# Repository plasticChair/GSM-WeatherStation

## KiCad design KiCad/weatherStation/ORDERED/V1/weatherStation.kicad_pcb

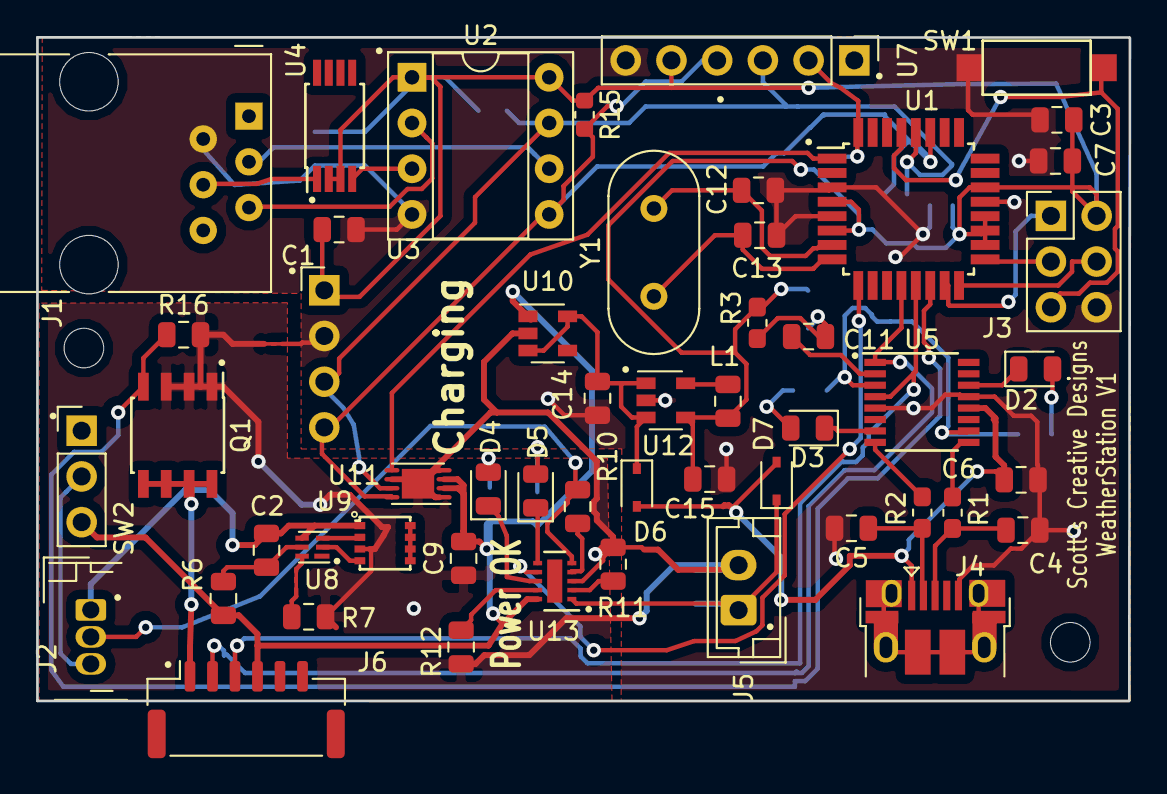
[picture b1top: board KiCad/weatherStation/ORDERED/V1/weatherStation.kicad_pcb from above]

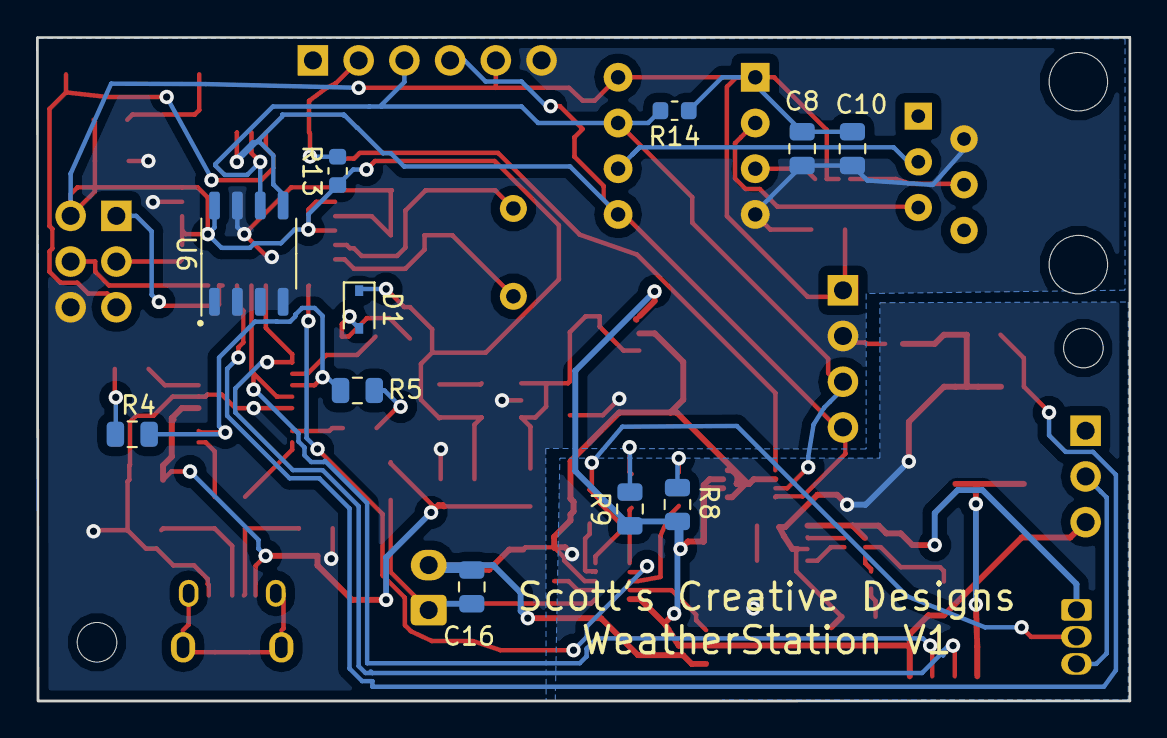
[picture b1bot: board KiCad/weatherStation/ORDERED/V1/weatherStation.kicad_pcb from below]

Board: 2 copper layers, 60.7 x 36.9 mm, 65 parts (11 on the bottom side), 54 nets.

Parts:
C1, C3, C6, C7, C8, C10, C11: 100nF; C_0805_2012Metric
C2, C9, C16: 0.1uF; C_0805_2012Metric
C4, C5: 47pF; C_0805_2012Metric
C12, C13: 22nF; C_0805_2012Metric
C14: 4.7uF; C_0805_2012Metric
C15: 10uF; C_0805_2012Metric
D1: D; D_SOD-323
D2: TXLED; LED_0805_2012Metric
D3: RXLED; LED_0805_2012Metric
D4, D5: LED; LED_0805_2012Metric
D6, D7: D_Schottky; D_SOD-323
J1: RJ12; RJ12_Amphenol_54601
J2: Conn_01x03; JST_EH_B03B-EH-A_1x03_P1.50mm_Vertical
J3: AVR-ISP-6; PinHeader_2x03_P2.54mm_Vertical
J4: USB_B_Micro; USB_Micro-B_Amphenol_10103594-0001LF_Horizontal
J5: Conn_01x02; JST_EH_B02B-EH-A_1x02_P2.50mm_Vertical
J6: Conn_01x04; JST_GH_SM06B-GHS-TB_1x06-1MP_P1.25mm_Horizontal
L1: 2.2uH; L_0805_2012Metric
Q1: AO4430; SOIC-8_3.9x4.9mm_P1.27mm
R1, R2: 27R; R_0603_1608Metric_Pad1.05x0.95mm_HandSolder
R3: 100k; R_0603_1608Metric_Pad1.05x0.95mm_HandSolder
R4, R5: 270R; R_0805_2012Metric
R6, R8, R9, R11, R12, R16: 330; R_0805_2012Metric
R7: 2.2k; R_0805_2012Metric
R10: RT; R_0805_2012Metric
R13: 50k; R_0603_1608Metric
R14, R15: 5k; R_0603_1608Metric
SW1: SW_Push; Tact_SMD_Switch
SW2: SW_SPDT; PinHeader_1x03_P2.54mm_Vertical
U1: ATmega328P-AU; TQFP-32_7x7mm_P0.8mm
U2: ATtiny45V-10PU; DIP-8_W7.62mm_Socket
U3: BME280; PinHeader_1x04_P2.54mm_Horizontal
U4: FDW254p; TSSOP-8_4.4x3mm_P0.65mm
U5: FT230XS; SSOP-16_3.9x4.9mm_P0.635mm
U6: MB85RC64; SSOP-8_3.9x5.05mm_P1.27mm
U7: DS3231_Breakout; PinHeader_1x06_P2.54mm_Vertical
U8: BQ297xy; WSON-6_1.5x1.5mm_P0.5mm
U9: ECH8693R; sot-28
U10: MAX40200; SOT-23-5
U11: MAX17048; TDFN-8-1EP_3x2mm_P0.5mm_EP1.80x1.65mm
U12: LM3671; SOT-23-5
U13: BQ24210; WSON-10-1EP_2x3mm_P0.5mm_EP0.84x2.4mm
W1, W3: Wire_Jump; wireJump
Y1: Crystal; Crystal_HC49-U_Vertical

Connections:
3V3: C1.2, C3.1, C7.1, C8.1, C10.1, C15.2, D1.1, J3.2, L1.2, R3.2, R13.1, R14.1, R15.1, U1.4, U1.6, U1.18, U1.19, U1.20, U1.22, U2.1, U2.8, U3.1, U4.2, U4.3, U6.8, U7.5, U12.4
/ANE_Pulse: J1.3, U2.6
/ANE_Tx: J1.5, U2.2
/ANE_Vcc: J1.4, U4.1
/ANE_Vcc_EN: U2.3, U4.4
/MISO: J3.1, U1.15
/MOSI: J3.4, U1.16
/RESET: J3.5, SW1.1, U1.29
/RTC_INT: R13.2, U1.32, U7.2
/RTS: C11.2, U5.2
/SCK: J3.3, U1.17
/Sheet5C1E5C91/Batt+: C9.2, J6.4, R6.1, R8.1, R9.1, SW2.3, U10.1, U11.2, U11.3, U13.10
/Sheet5C1E5C91/Batt-: C2.2, J2.1, U8.4, U9.1
/Sheet5C1E5C91/NTC: J2.2, R10.1, U13.5
/Sheet5C1E5C91/Pack-: C9.1, C16.2, J5.2, Q1.1, Q1.2, Q1.3, R7.2, R11.2, R12.2, R16.2, U9.3, U10.2, U11.1, U11.4, U11.6, U11.9, U13.3, W1.1
/Sheet5C1E5C91/SIM-: J6.1, Q1.5, Q1.6, Q1.7, Q1.8
/Sheet5C1E5C91/Solar+: C16.1, D7.1, J5.1, U13.1
/XTAL1: C12.1, U1.7, Y1.2
/XTAL2: C13.1, U1.8, Y1.1
BATT_ALRT: U1.1, U11.5
Charge_EN: U1.9, U13.7
GND: C1.1, C3.2, C4.2, C5.2, C6.1, C7.2, C8.2, C10.2, C12.2, C13.2, C14.1, C15.1, J1.2, J3.6, J4.5, SW1.2, U1.3, U1.5, U1.21, U2.4, U3.2, U5.5, U5.13, U6.1, U6.2, U6.3, U6.4, U6.7, U7.6, U12.2, W1.2
I2C_SCL: R14.2, U1.28, U2.7, U3.3, U6.6, U7.3, U11.7
I2C_SDA: R15.2, U1.27, U2.5, U3.4, U6.5, U7.4, U11.8
unnamed: C2.1, R6.2, U8.5
unnamed: C4.1, J4.3, R1.2
unnamed: C5.1, J4.2, R2.2
unnamed: C11.1, D1.2, R3.1
unnamed: C14.2, D6.1, U10.3, U10.5, U12.1, U12.3
unnamed: D2.1, U5.14
unnamed: D2.2, R4.1
unnamed: D3.1, U5.7
unnamed: D3.2, R5.1
unnamed: D4.1, U13.8
unnamed: D4.2, R8.2
unnamed: D5.1, U13.6
unnamed: D5.2, R9.2
unnamed: J2.3, SW2.2
unnamed: L1.1, U12.5
unnamed: R1.1, U5.9
unnamed: R2.1, U5.8
unnamed: R4.2, R5.2, U5.3, U5.10
unnamed: R7.1, W3.1
unnamed: R10.2, U13.4
unnamed: R11.1, U13.2
unnamed: R12.1, U13.9
unnamed: U8.2, U9.4
unnamed: U8.3, U9.2
unnamed: U8.6, W3.2
unnamed: U9.5, U9.6, U9.7, U9.8
Rx: J6.2, U1.12, U5.1
SIM_EN: Q1.4, R16.1, U1.14
Tx: J6.3, U1.13, U5.4
USB_PWR: C6.2, D6.2, D7.2, J4.1, U5.12

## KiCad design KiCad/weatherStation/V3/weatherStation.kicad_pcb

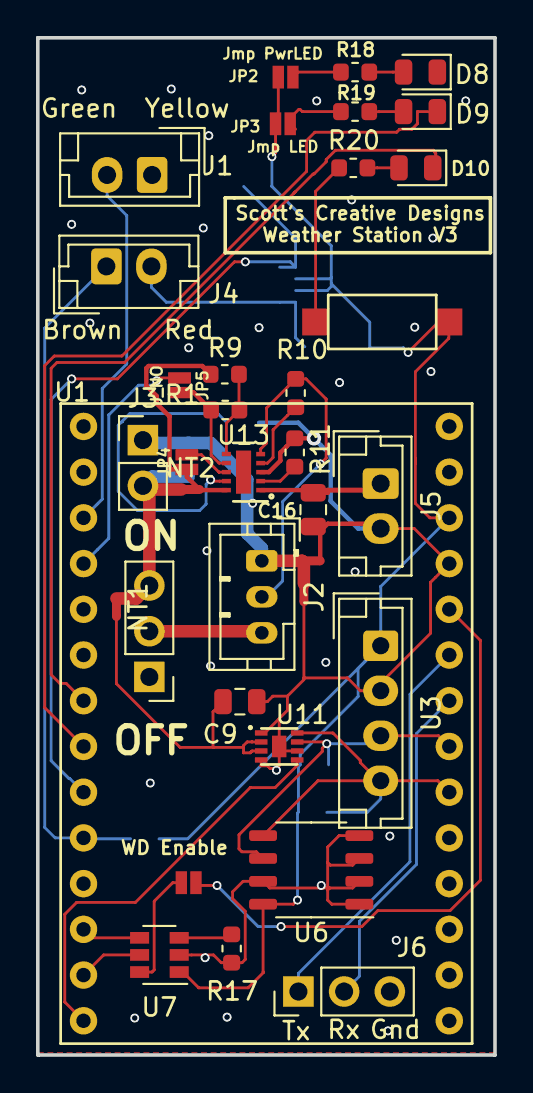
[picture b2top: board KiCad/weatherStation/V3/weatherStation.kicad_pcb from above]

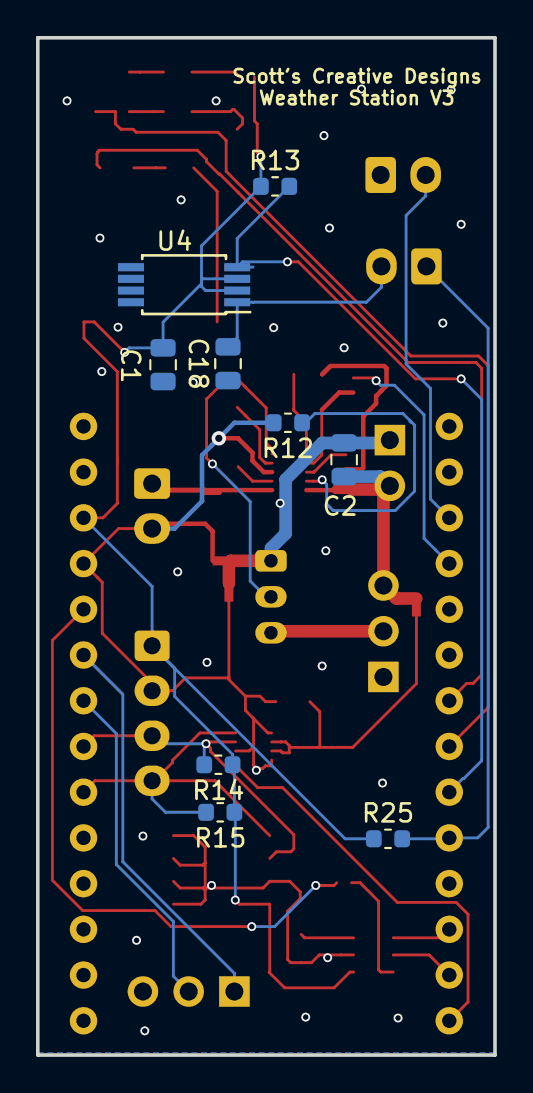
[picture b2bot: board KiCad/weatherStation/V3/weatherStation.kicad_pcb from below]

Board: 2 copper layers, 25.4 x 56.5 mm, 45 parts (9 on the bottom side), 37 nets.

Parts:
C1, C18: 100nF; C_0805_2012Metric
C2, C16: 1uF; C_0805_2012Metric
C9: 0.1uF; C_0805_2012Metric
D8: 3V3 OK; LED_0805_2012Metric
D9, D10: GPLED; LED_0805_2012Metric
J1, J4, J5: Conn_01x02; JST_EH_B02B-EH-A_1x02_P2.50mm_Vertical
J2: Conn_01x03; JST_PH_B3B-PH-K_1x03_P2.00mm_Vertical
J3: Conn_01x02_Female; PinHeader_1x02_P2.54mm_Vertical
J6: Conn_01x03_Female; PinHeader_1x03_P2.54mm_Vertical
JP1: Jmp_NO; SMT-JUMPER_2_NO_NO-SILK
JP2: Jmp PwrLED; SMT-JUMPER_2_NO_NO-SILK
JP3: Jmp LED; SMT-JUMPER_2_NO_NO-SILK
JP4, JP5: J_NO; SMT-JUMPER_2_NO_NO-SILK
NT1, NT2, NT3, NT4: Net-Tie_2; NetTie-2_SMD_Pad0.5mm
R1, R13, R25: 10k; R_0603_1608Metric
R9: 100k; R_0603_1608Metric
R10: RT; R_0603_1608Metric
R11: 750; R_0603_1608Metric
R12: 330; R_0603_1608Metric
R14, R15: 5k; R_0603_1608Metric
R17: 33k; R_0603_1608Metric
R18, R19, R20: 300; R_0603_1608Metric
SW2: SW_SPDT; PinHeader_1x03_P2.54mm_Vertical
SW3: LED_Push; Tact_SMD_Switch
U1: MKRGSM1400
U3: BME280; JST_EH_B04B-EH-A_1x04_P2.50mm_Vertical
U4: FDW254p; TSSOP-8_4.4x3mm_P0.65mm
U6: MB85RC64; SSOP-8_3.9x5.05mm_P1.27mm
U7: TPL5010; SOT-23-6
U11: MAX17048; TQFN-8_2x2x0.75
U13: BQ24210; WSON-10-1EP_2x3mm_P0.5mm_EP0.84x2.4mm

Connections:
3V3: C1.2, JP2.2, JP3.1, R13.1, R14.1, R15.1, R25.1, SW3.1, U1.26, U3.1, U4.2, U4.3, U6.8, U7.1
/ANE_Pulse: J1.2, U1.3
/ANE_Tx: J4.1, R25.2, U1.10
/ANE_Vcc: C18.2, J4.2, U4.1
/ANE_Vcc_EN: R13.2, U1.9, U4.4
/DONE: U1.12, U7.4
/GPLED1: D9.1, U1.8
/GPLED2: D10.1, U1.7
/RESET: JP1.2, U1.24
/Sheet5C1E5C91/Batt+: C2.1, J3.2, NT1.1, NT2.1, SW2.3
/Sheet5C1E5C91/BattMon+: C9.2, NT1.2, U11.2, U11.3
/Sheet5C1E5C91/Batt_Chrg+: JP4.1, NT2.2, R9.1, U13.10
/Sheet5C1E5C91/Batt_int: J2.3, SW2.2
/Sheet5C1E5C91/NTC: J2.2, R10.2, U13.5
/Sheet5C1E5C91/Solar+: C16.1, J5.1, U13.1
/WAKE: U1.13, U7.5
BATT_ALRT: U1.14, U11.5
CHRG_EN: JP5.1, U1.4
GND: C1.1, C2.2, C9.1, C16.2, C18.1, D8.1, J1.1, J2.1, J3.1, J5.2, J6.3, NT3.1, NT3.2, NT4.1, NT4.2, R11.2, R12.2, R17.1, U1.25, U3.2, U6.1, U6.2, U6.3, U6.4, U6.7, U7.2, U11.1, U11.4, U11.6, U11.9, U13.3
I2C_SCL: R14.2, U1.21, U3.3, U6.6, U11.7
I2C_SDA: R15.2, U1.20, U3.4, U6.5, U11.8
unnamed: D8.2, R18.1
unnamed: D9.2, R19.2
unnamed: D10.2, R20.1
unnamed: J6.1, U1.23
unnamed: J6.2, U1.22
unnamed: JP1.1, U7.6
unnamed: JP2.1, R18.2
unnamed: JP3.2, R19.1
unnamed: JP4.2, U13.8
unnamed: JP5.2, R1.2, U13.7
unnamed: R1.1, R9.2, U13.6
unnamed: R10.1, U13.4
unnamed: R11.1, U13.2
unnamed: R12.1, U13.9
unnamed: R17.2, U7.3
unnamed: R20.2, SW3.2

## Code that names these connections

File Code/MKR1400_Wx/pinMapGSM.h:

// pinMapGSM.h

#ifndef _PINMAPGSM_h
#define _PINMAPGSM_h

#if defined(ARDUINO) && ARDUINO >= 100
	#include "arduino.h"
#else
	#include "WProgram.h"
#endif


#define GPLED1 A6
#define GPLED2 A5
#define ANE_Vcc_EN 0
#define ANE_TX 1
#define ANE_PULSE A1
#define DONE 3
#define WAKE 4
#define BATT_ALRT 5
#define I2C_SCL 12
#define I2C_SDA 11

#define CHARGE_EN A2


#endif

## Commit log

2019-05-16 init commit of git. Working board and website
2019-10-07 Commit before server update
2019-10-24 commit before more
